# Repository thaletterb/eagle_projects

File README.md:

# Eagle Projects Repository

A repo to store my eagle projects and lbr files storing my custom parts

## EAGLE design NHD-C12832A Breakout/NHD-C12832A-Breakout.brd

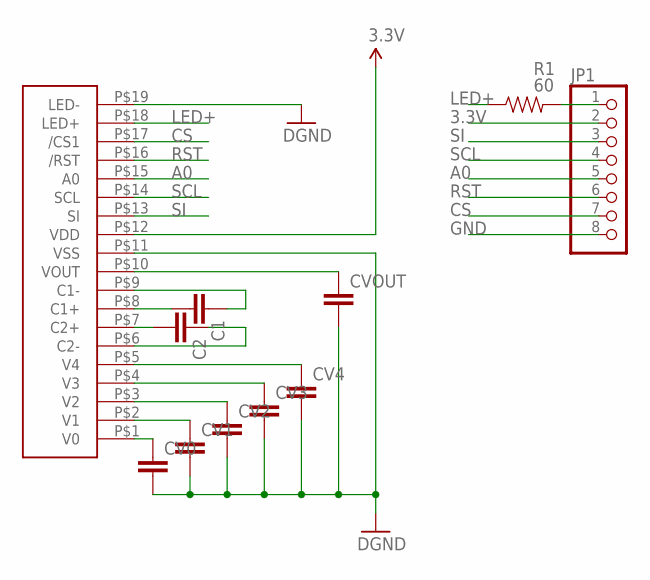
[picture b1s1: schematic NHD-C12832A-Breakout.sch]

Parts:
C1, C2: C-EUC0805; C0805
CV0, CV1, CV2, CV3, CV4: C-EUC0805; C0805
CVOUT: C-EUC0805; C0805
JP1: PINHD-1X8; 1X08
R1: 60; 0805
U$1: NHD-C12832A; NHD-C12832A-PACK

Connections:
3.3V: JP1.2, U$1.P$12 (VDD)
A0: JP1.5, U$1.P$15 (A0)
CS: JP1.7, U$1.P$17 (/CS1)
GND: CV0.2, CV1.2, CV2.2, CV3.2, CV4.2, CVOUT.2, JP1.8, U$1.P$11 (VSS), U$1.P$19 (LED-)
LED+: R1.1, U$1.P$18 (LED+)
unnamed: CV4.1, U$1.P$5 (V4)
unnamed: CV3.1, U$1.P$4 (V3)
unnamed: CV2.1, U$1.P$3 (V2)
unnamed: CV1.1, U$1.P$2 (V1)
unnamed: CV0.1, U$1.P$1 (V0)
unnamed: CVOUT.1, U$1.P$10 (VOUT)
unnamed: C1.1, U$1.P$9 (C1-)
unnamed: C1.2, U$1.P$8 (C1+)
unnamed: C2.2, U$1.P$7 (C2+)
unnamed: C2.1, U$1.P$6 (C2-)
unnamed: JP1.1, R1.2
RST: JP1.6, U$1.P$16 (/RST)
SCL: JP1.4, U$1.P$14 (SCL)
SI: JP1.3, U$1.P$13 (SI)

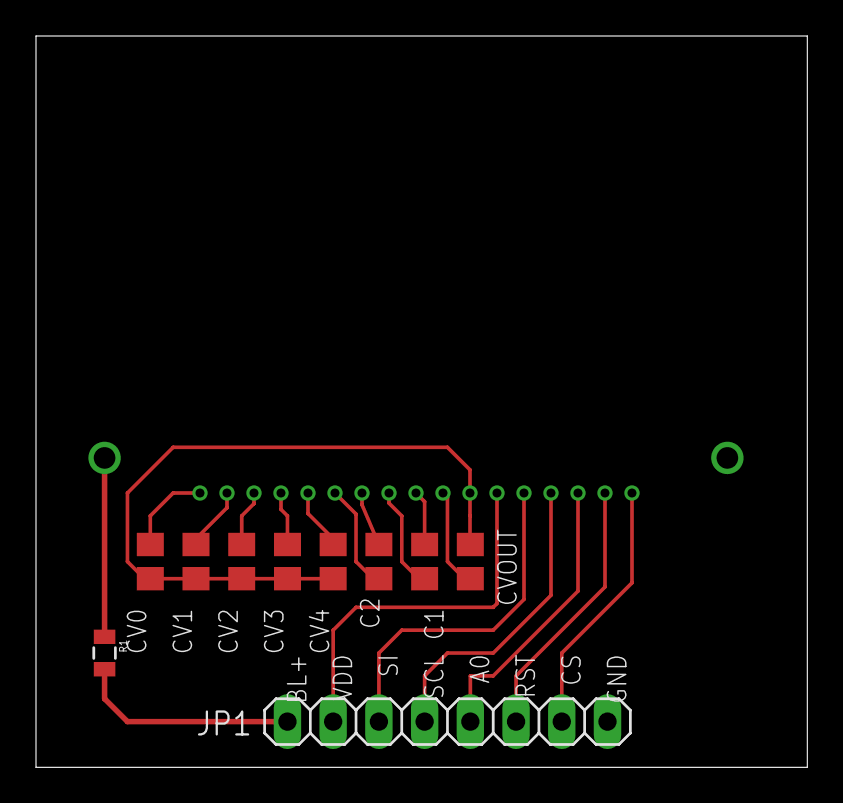
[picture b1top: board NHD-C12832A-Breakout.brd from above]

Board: 2 copper layers, 42.9 x 40.6 mm, 11 parts (0 on the bottom side), 19 nets.

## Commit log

2016-03-04 add readme file
2016-03-04 add eagle temp files to gitignore
2016-03-04 first commit of NHD-C1238A Breakout project
2016-03-04 Add NHD-C12832A DS

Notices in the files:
parts and their libraries:
SparkFun-Resistors: Licensing: Creative Commons ShareAlike 4.0 International - https://creativecommons.org/licenses/by-sa/4.0
